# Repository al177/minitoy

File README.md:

Dead-end personal project for a WiFi enabled FPGA board using the Lattice ICE40UP5K FPGA.

Features:

- Minimal-ish part count due to using the ESP8266 to configure the FPGA during power-up
- Intended to run Micropython
- Fast SPI channel between ICE40 and ES8266 can be used as a communications channel after boot

This project has been built as of the 0.1 revision of the PCB. There are numerous workarounds needed to get it running that are
rolled up into the v0.2 PCB committed here, though v0.2 has not been manufactured.

Possible improvements:

- ESP32 instead of ESP8266 for an additional serial port for a separate console, additional horsepower, and lower power modes.
- Reset button
- Combine both 3.3v LDOs since I don't think sequencing 1.2 before 3.3 is that critical for the ICE40
- Fix RGB LED pinout
- Fix reset circuit for ESP (in v0.2)
- 0 ohm resistor to take 5v power from FTDI cable
- LiFePO4 or LiPo power

Included are iceboot.py, a Micropython module that can boot an ICE40 bitstream, and boot.py which is a startup script to load a
bitstream on Micropython power-up.

*** If you wish to use iceboot.py with modern Micropython, please use the currently maintained version here: https://github.com/al177/blinkencard/blob/master/micropython/iceboot.py . The version here is specific to an old version of the LoBoris fork, and the machine API for SPI has changed since.

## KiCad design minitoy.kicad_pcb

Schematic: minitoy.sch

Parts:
C1, C3, C5, C11, C13, C14, C25: 0.1uF; C_0603_HandSoldering
C2, C6: 1uF; C_0603_HandSoldering
C4, C10, C12: 0.01uF; C_0603_HandSoldering
C16, C17, C19, C20, C22, C23: 1.0uF; C_0603_HandSoldering
C18, C21, C24: 47uF; CP_Elec_5x5.3
D1: LED_ARGB; LED_Cree-PLCC4_3.2x2.8mm_CCW
D10: D_Schottky; D_SOD-123
J1: Conn_01x06; Pin_Header_Straight_1x06_Pitch2.54mm
J2: PMOD1; Socket_Strip_Angled_2x06_Pitch2.54mm
J4: USB_B_Micro; USB_Micro-B_10103594-0001LF
J5: PMOD2; Socket_Strip_Angled_2x06_Pitch2.54mm
R1, R9, R10, R19, R20: 10k; R_0603_HandSoldering
R14: 100; R_0603_HandSoldering
U1: ICE40UP5K-SG48; QFN-48-1EP_7x7mm_Pitch0.5mm
U2: ESP-12E
U3, U5: MIC5504-3.3YM5; SOT-23-5_HandSoldering
U4: MIC5504-1.2YM5; SOT-23-5_HandSoldering

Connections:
+1V2: C4.1, C5.1, C6.1, C20.1, C21.1, R14.2, U1.5, U1.30, U3.3, U4.5 (VOUT)
+3.3VA: C23.1, C24.1, R1.2, R9.2, R10.2, R19.2, U2.8, U5.5
+3V3: C1.1, C3.1, C12.1, C13.1, C14.1, C17.1, C18.1, C25.1, D1.1, J2.11, J2.12, J5.11, J5.12, U1.1, U1.22, U1.24, U1.33, U3.5
/VCCPLL: C10.1, C11.1, R14.1, U1.29
ESP_PROG: C2.2, D10.1, J1.6
ESP_UART_RX: J1.4, U1.21, U2.21
ESP_UART_TX: J1.5, U1.20, U2.22
FPGA_CDONE: U1.7, U2.19
FPGA_CFG_MISO: U1.14, U2.6
FPGA_CFG_MOSI: U1.17, U2.7
FPGA_CFG_SCLK: U1.15, U2.5
FPGA_CFG_SS: R20.2, U1.16, U2.16
FPGA_CRESET: U1.8, U2.20
FPGA_INT: R19.1, U1.13, U2.17
GND: C1.2, C3.2, C4.2, C5.2, C6.2, C10.2, C11.2, C12.2, C13.2, C14.2, C16.2, C17.2, C18.2, C19.2, C20.2, C21.2, C22.2, C23.2, C24.2, C25.2, J1.1, J2.9, J2.10, J4.5, J4.6, J5.9, J5.10, R20.1, U1.9, U1.10, U1.11, U1.12, U1.28, U1.35, U1.36, U1.49, U2.15, U3.2, U4.2 (GND), U5.2
unnamed: C2.1, R9.1, U2.1
unnamed: D1.2, U1.41
unnamed: D1.3, U1.40
unnamed: D1.4, U1.39
unnamed: D10.2, R10.1, U2.18
unnamed: R1.1, U2.3
PMOD-1.1: J2.1, U1.25
PMOD-1.2: J2.3, U1.27
PMOD-1.3: J2.5, U1.31
PMOD-1.4: J2.7, U1.34
PMOD-1.7: J2.2, U1.23
PMOD-1.8: J2.4, U1.26
PMOD-1.9: J2.6, U1.32
PMOD-1.10: J2.8, U1.37
PMOD-2.1: J5.1, U1.44
PMOD-2.2: J5.3, U1.46
PMOD-2.3: J5.5, U1.48
PMOD-2.4: J5.7, U1.3
PMOD-2.7: J5.2, U1.45
PMOD-2.8: J5.4, U1.47
PMOD-2.9: J5.6, U1.2
PMOD-2.10: J5.8, U1.4
VDD: C16.1, C19.1, C22.1, J4.1, U3.1, U4.1 (VIN), U4.3 (EN), U5.1, U5.3

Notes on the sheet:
NOTE: OTP NVRAM programming is not possible with this VPP_2V5 configuration
I3C
FTDI 3.3V UART
DTR
TXD
RXD
GND
CTS

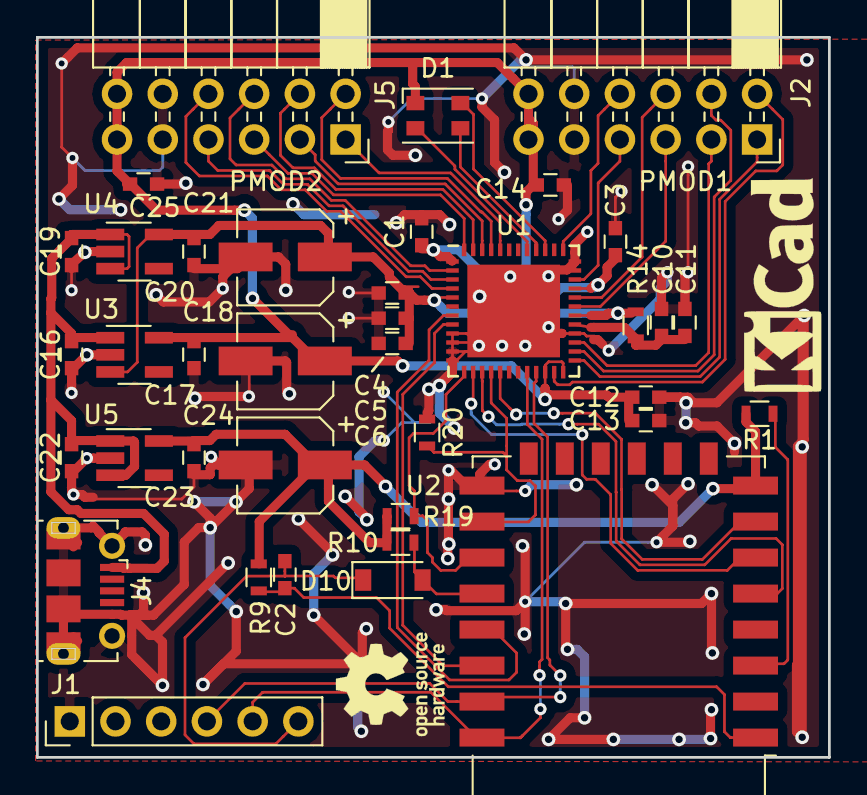
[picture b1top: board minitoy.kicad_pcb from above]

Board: 2 copper layers, 44.0 x 40.0 mm, 38 parts (0 on the bottom side), 38 nets.

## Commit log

2018-02-16 Initial import - work in progress
2018-02-17 Change ESP reset scheme and UART connection
2018-02-18 Rough schematic complete.
2018-02-19 Start layout
2018-02-19 Remove blinkenlights and buttons, add another PMOD socket
2018-02-19 More consolidation of the board
2018-02-20 More layout changes, remove a PMOD socket for easier routing
2018-02-22 Routing done, but cleanup needed
2018-02-22 Routing complete. Next up, fix silk.
2018-02-22 Fix 3d models, change USB footprint
2018-02-23 Finish silk, fix USB cutout for OSH Park, finalize design
2018-02-23 Generate gerbers, RTM
2018-02-23 Last minute fix for possible short
2018-03-11 v0.2: fix ESP POR straps and reset, fix typo on serial connector
2019-11-09 Add Micropython fw boot modules, and README.
